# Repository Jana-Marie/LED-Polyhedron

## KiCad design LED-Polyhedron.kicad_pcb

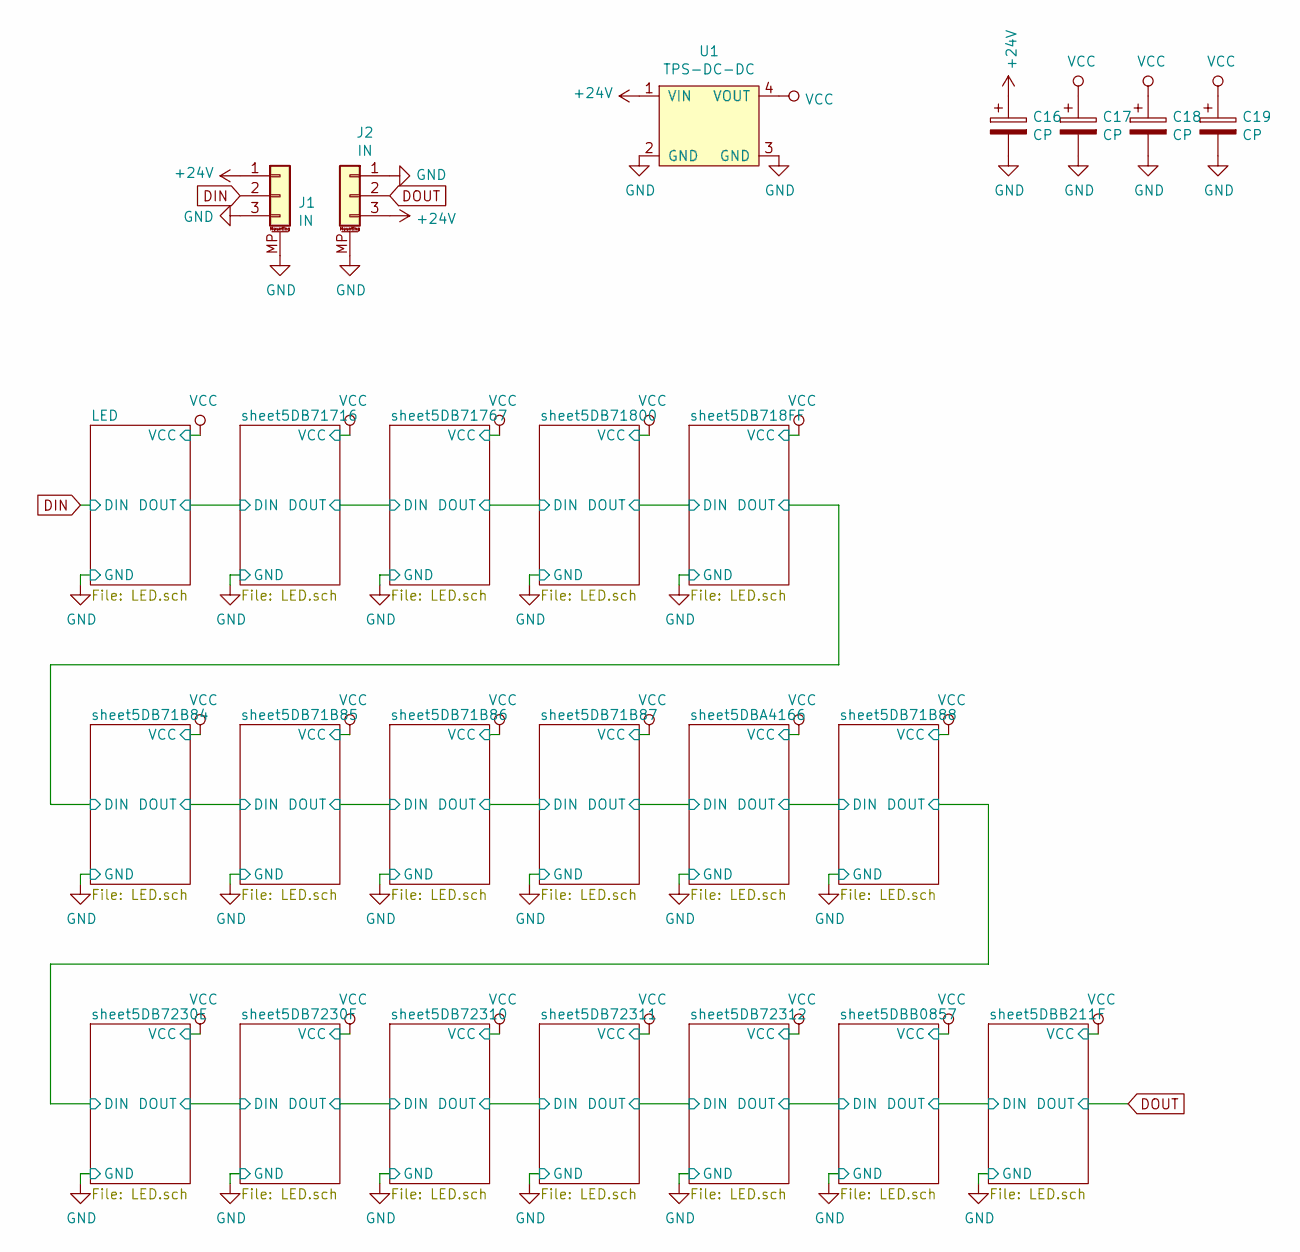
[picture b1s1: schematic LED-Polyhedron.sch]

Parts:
C16, C17, C18, C19: CP; C-THT-as-SMD
J1, J2: IN; JST_PH_S3B-PH-SM4-TB_1x03-1MP_P2.00mm_Horizontal
U1: TPS-DC-DC; LM2596-DC-DC

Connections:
+24V: C16.1, J1.1, J2.3, U1.1 (VIN)
DIN: J1.2; also elsewhere on the board
DOUT: J2.2; also elsewhere on the board
GND: C16.2, C17.2, C18.2, C19.2, J1.3, J1.MP (MountPin), J2.1, J2.MP (MountPin), U1.2 (GND), U1.3 (GND); also elsewhere on the board
VCC: C17.1, C18.1, C19.1, U1.4 (VOUT); also elsewhere on the board

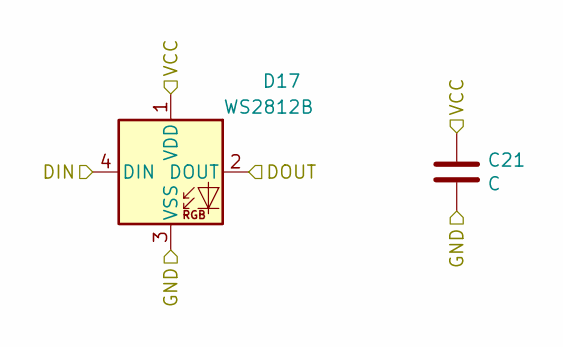
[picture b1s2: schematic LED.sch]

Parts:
C1: C; C_0603_1608Metric
D1: WS2812B; LED_WS2812B_PLCC4_5.0x5.0mm_P3.2mm

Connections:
/sheet5DB71716/DIN: D1.2 (DOUT); also elsewhere on the board
DIN: D1.4 (DIN); also elsewhere on the board
GND: C1.2, D1.3 (VSS); also elsewhere on the board
VCC: C1.1, D1.1 (VDD); also elsewhere on the board

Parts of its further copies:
C2, C3, C4, C5, C6, C7, C8, C9, C10, C11, C12, C13, C14, C15, C20, C21, C22: C; C_0603_1608Metric
D2, D3, D4, D5, D6, D7, D8, D9, D10, D11, D12, D13, D14, D15, D16, D17, D18: WS2812B; LED_WS2812B_PLCC4_5.0x5.0mm_P3.2mm

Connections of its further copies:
/sheet5DB71B84/DIN: D5.2 (DOUT), D6.4 (DIN)
/sheet5DB71B85/DIN: D6.2 (DOUT), D7.4 (DIN)
/sheet5DB71B86/DIN: D7.2 (DOUT), D8.4 (DIN)
/sheet5DB71B87/DIN: D8.2 (DOUT), D9.4 (DIN)
/sheet5DB71B88/DIN: D10.4 (DIN), D16.2 (DOUT)
/sheet5DB718FF/DIN: D4.2 (DOUT), D5.4 (DIN)
/sheet5DB7230E/DIN: D10.2 (DOUT), D11.4 (DIN)
/sheet5DB7230F/DIN: D11.2 (DOUT), D12.4 (DIN)
/sheet5DB71716/DIN: D2.4 (DIN); also elsewhere on the board
/sheet5DB71767/DIN: D2.2 (DOUT), D3.4 (DIN)
/sheet5DB71800/DIN: D3.2 (DOUT), D4.4 (DIN)
/sheet5DB72310/DIN: D12.2 (DOUT), D13.4 (DIN)
/sheet5DB72311/DIN: D13.2 (DOUT), D14.4 (DIN)
/sheet5DB72312/DIN: D14.2 (DOUT), D15.4 (DIN)
/sheet5DBA4166/DIN: D9.2 (DOUT), D16.4 (DIN)
/sheet5DBB211F/DIN: D17.2 (DOUT), D18.4 (DIN)
/sheet5DBB0857/DIN: D17.4 (DIN); also elsewhere on the board
/sheet5DD4437B/DIN: D15.2 (DOUT); also elsewhere on the board
DOUT: D18.2 (DOUT); also elsewhere on the board
GND: C2.2, C3.2, C4.2, C5.2, C6.2, C7.2, C8.2, C9.2, C10.2, C11.2, C12.2, C13.2, C14.2, C15.2, C20.2, C21.2, C22.2, D2.3 (VSS), D3.3 (VSS), D4.3 (VSS), D5.3 (VSS), D6.3 (VSS), D7.3 (VSS), D8.3 (VSS), D9.3 (VSS), D10.3 (VSS), D11.3 (VSS), D12.3 (VSS), D13.3 (VSS), D14.3 (VSS), D15.3 (VSS), D16.3 (VSS), D17.3 (VSS), D18.3 (VSS); also elsewhere on the board
VCC: C2.1, C3.1, C4.1, C5.1, C6.1, C7.1, C8.1, C9.1, C10.1, C11.1, C12.1, C13.1, C14.1, C15.1, C20.1, C21.1, C22.1, D2.1 (VDD), D3.1 (VDD), D4.1 (VDD), D5.1 (VDD), D6.1 (VDD), D7.1 (VDD), D8.1 (VDD), D9.1 (VDD), D10.1 (VDD), D11.1 (VDD), D12.1 (VDD), D13.1 (VDD), D14.1 (VDD), D15.1 (VDD), D16.1 (VDD), D17.1 (VDD), D18.1 (VDD); also elsewhere on the board

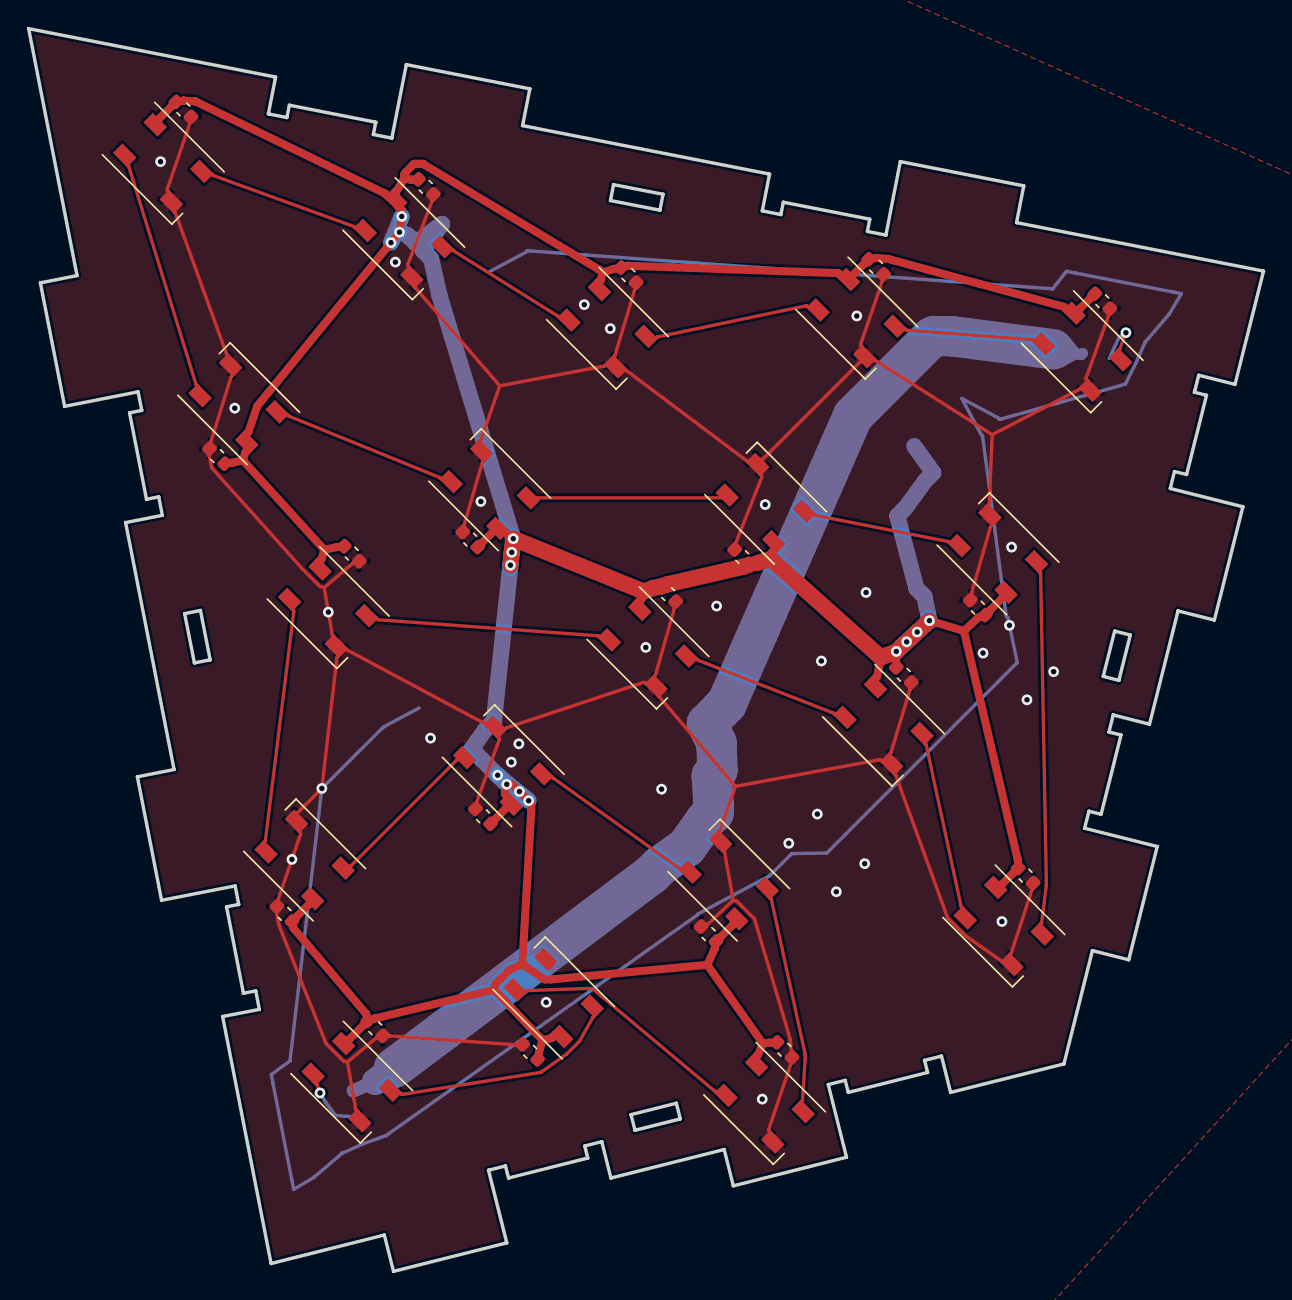
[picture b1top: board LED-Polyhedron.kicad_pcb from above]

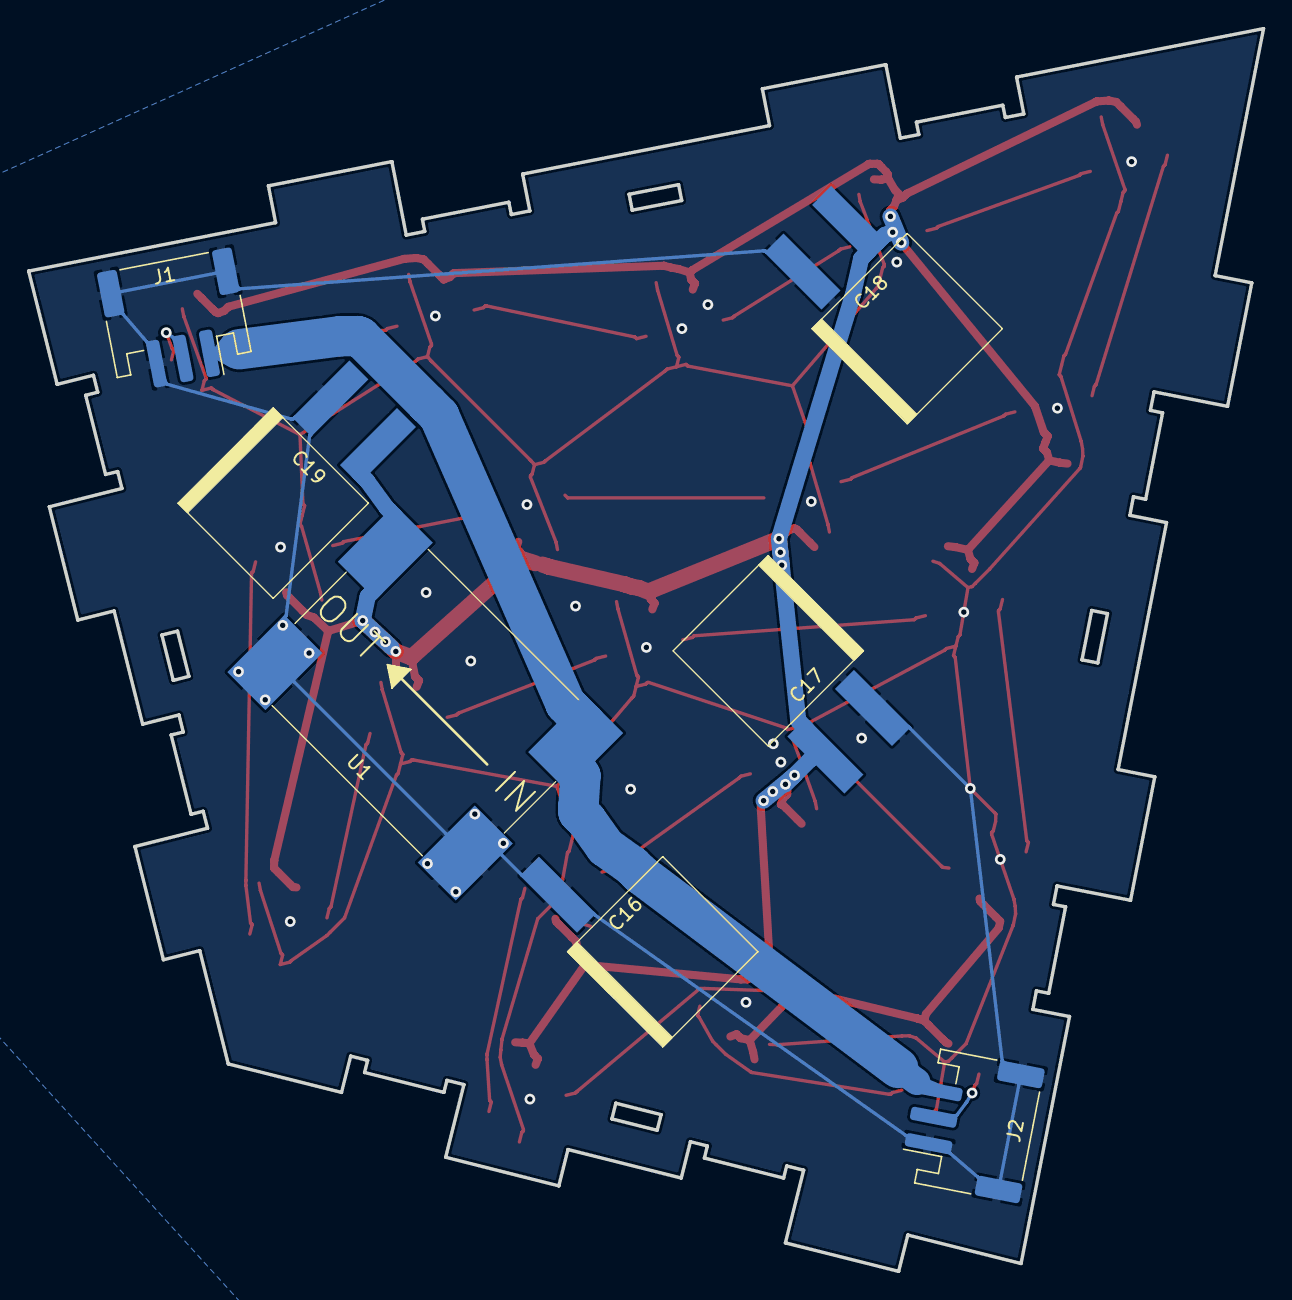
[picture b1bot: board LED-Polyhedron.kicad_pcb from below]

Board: 2 copper layers, 91.7 x 92.3 mm, 46 parts (7 on the bottom side), 23 nets.

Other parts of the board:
C23: C; C_0603_1608Metric
D19: WS2812B; LED_WS2812B_PLCC4_5.0x5.0mm_P3.2mm
otter: otter

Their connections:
/sheet5DBB0857/DIN: D19.2; also elsewhere on the board
/sheet5DD4437B/DIN: D19.4; also elsewhere on the board
GND: C23.2, D19.3; also elsewhere on the board
VCC: C23.1, D19.1; also elsewhere on the board

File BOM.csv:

Comment,Designator,Footprint,LCSC
C,"C1,C2,C3,C4,C5,C6,C7,C8,C9,C10,C11,C12,C13,C14,C15,C20,C21,C22",Capacitor_SMD:C_0603_1608Metric,C14663
CP,"C16,C17,C18,C19",otter:C-THT-as-SMD,
WS2812B,"D1,D2,D3,D4,D5,D6,D7,D8,D9,D10,D11,D12,D13,D14,D15,D16,D17,D18",LED_SMD:LED_WS2812B_PLCC4_5.0x5.0mm_P3.2mm,C114587
IN,"J1,J2",Connector_JST:JST_PH_S3B-PH-SM4-TB_1x03-1MP_P2.00mm_Horizontal,
TPS-DC-DC,U1,otter:LM2596-DC-DC,

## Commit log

2019-10-30 added files
2019-11-20 added topor files
